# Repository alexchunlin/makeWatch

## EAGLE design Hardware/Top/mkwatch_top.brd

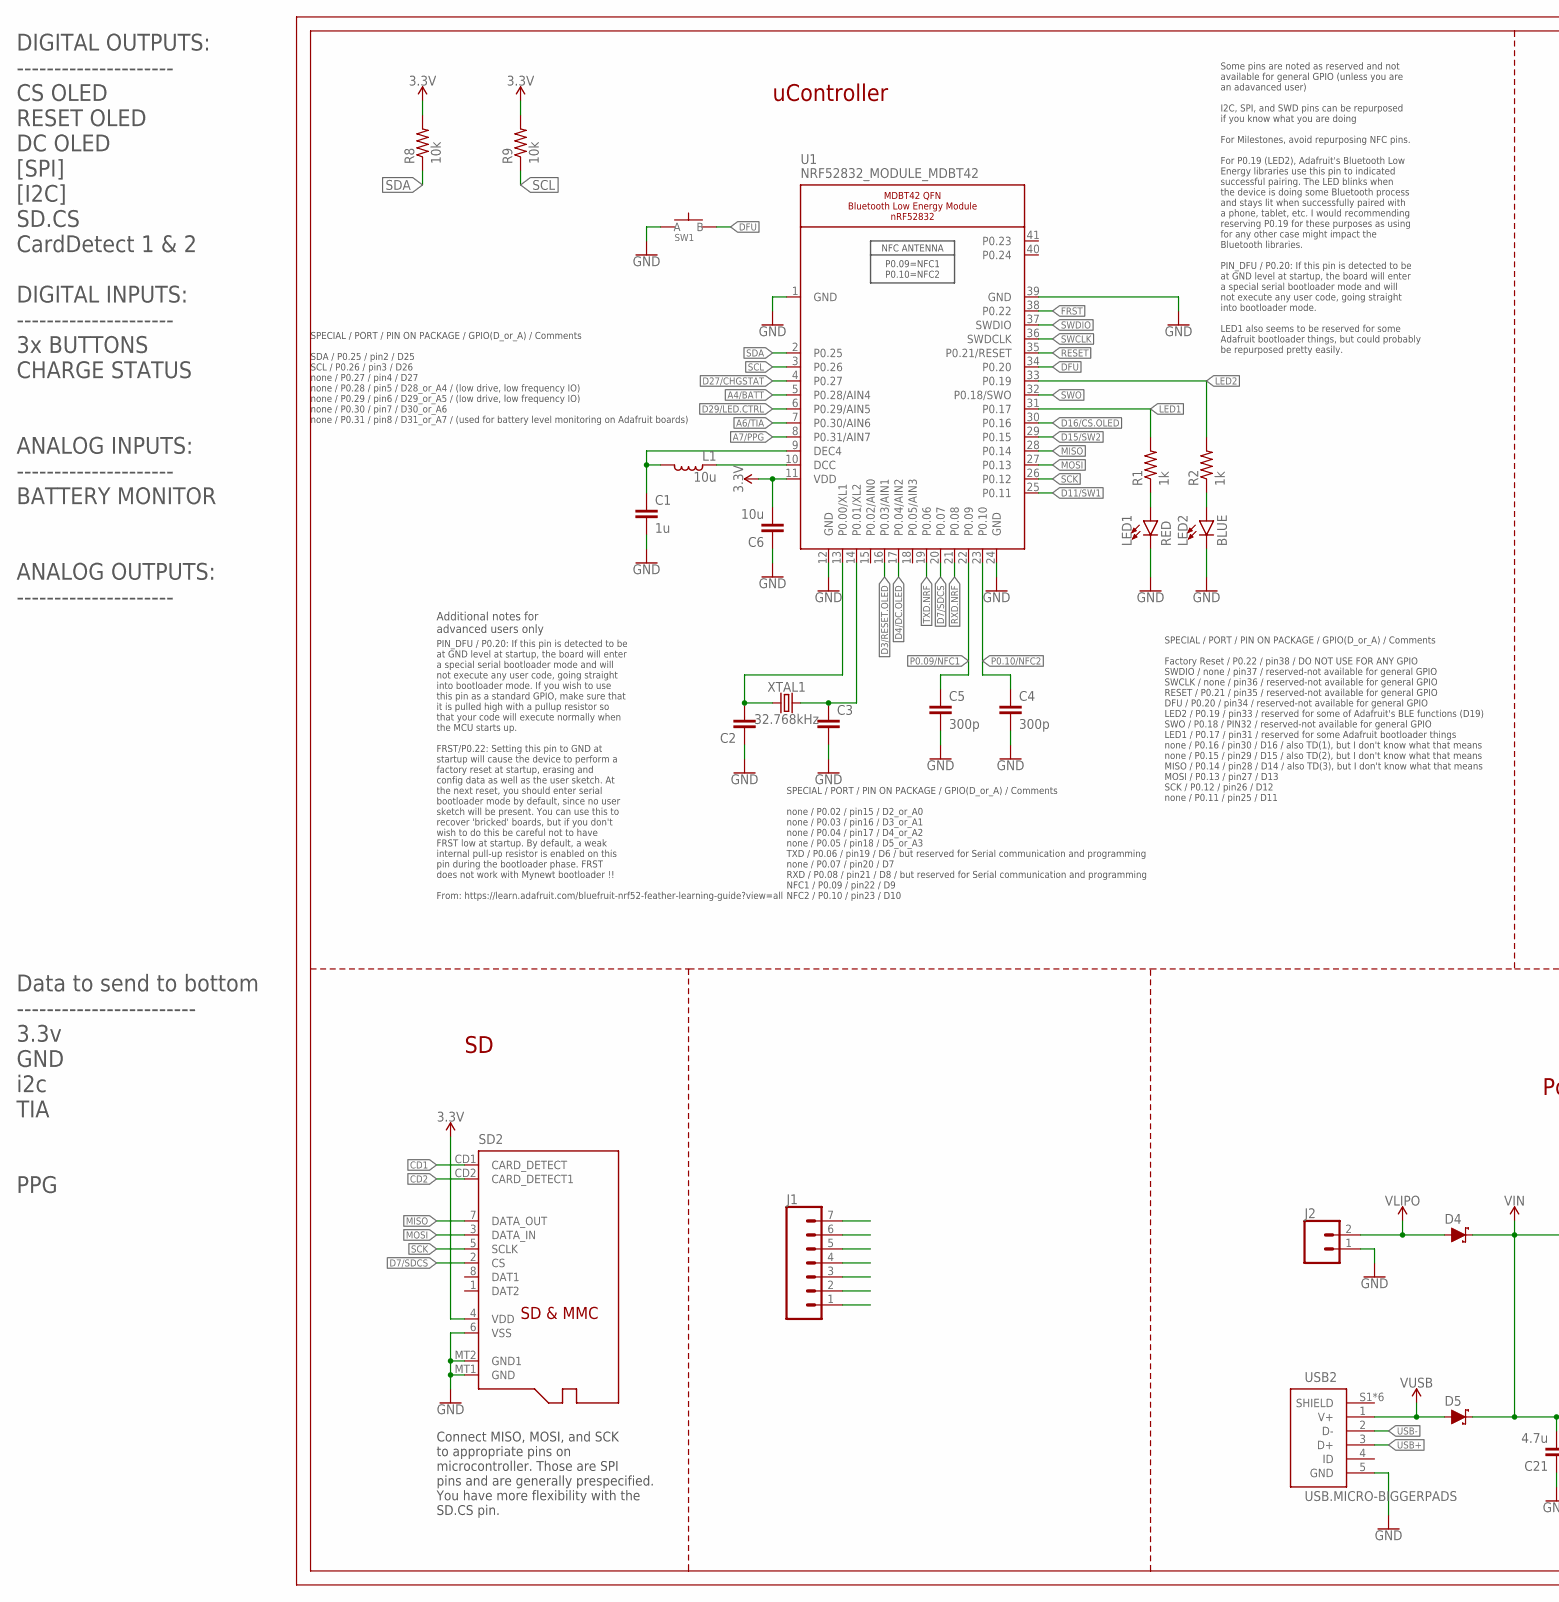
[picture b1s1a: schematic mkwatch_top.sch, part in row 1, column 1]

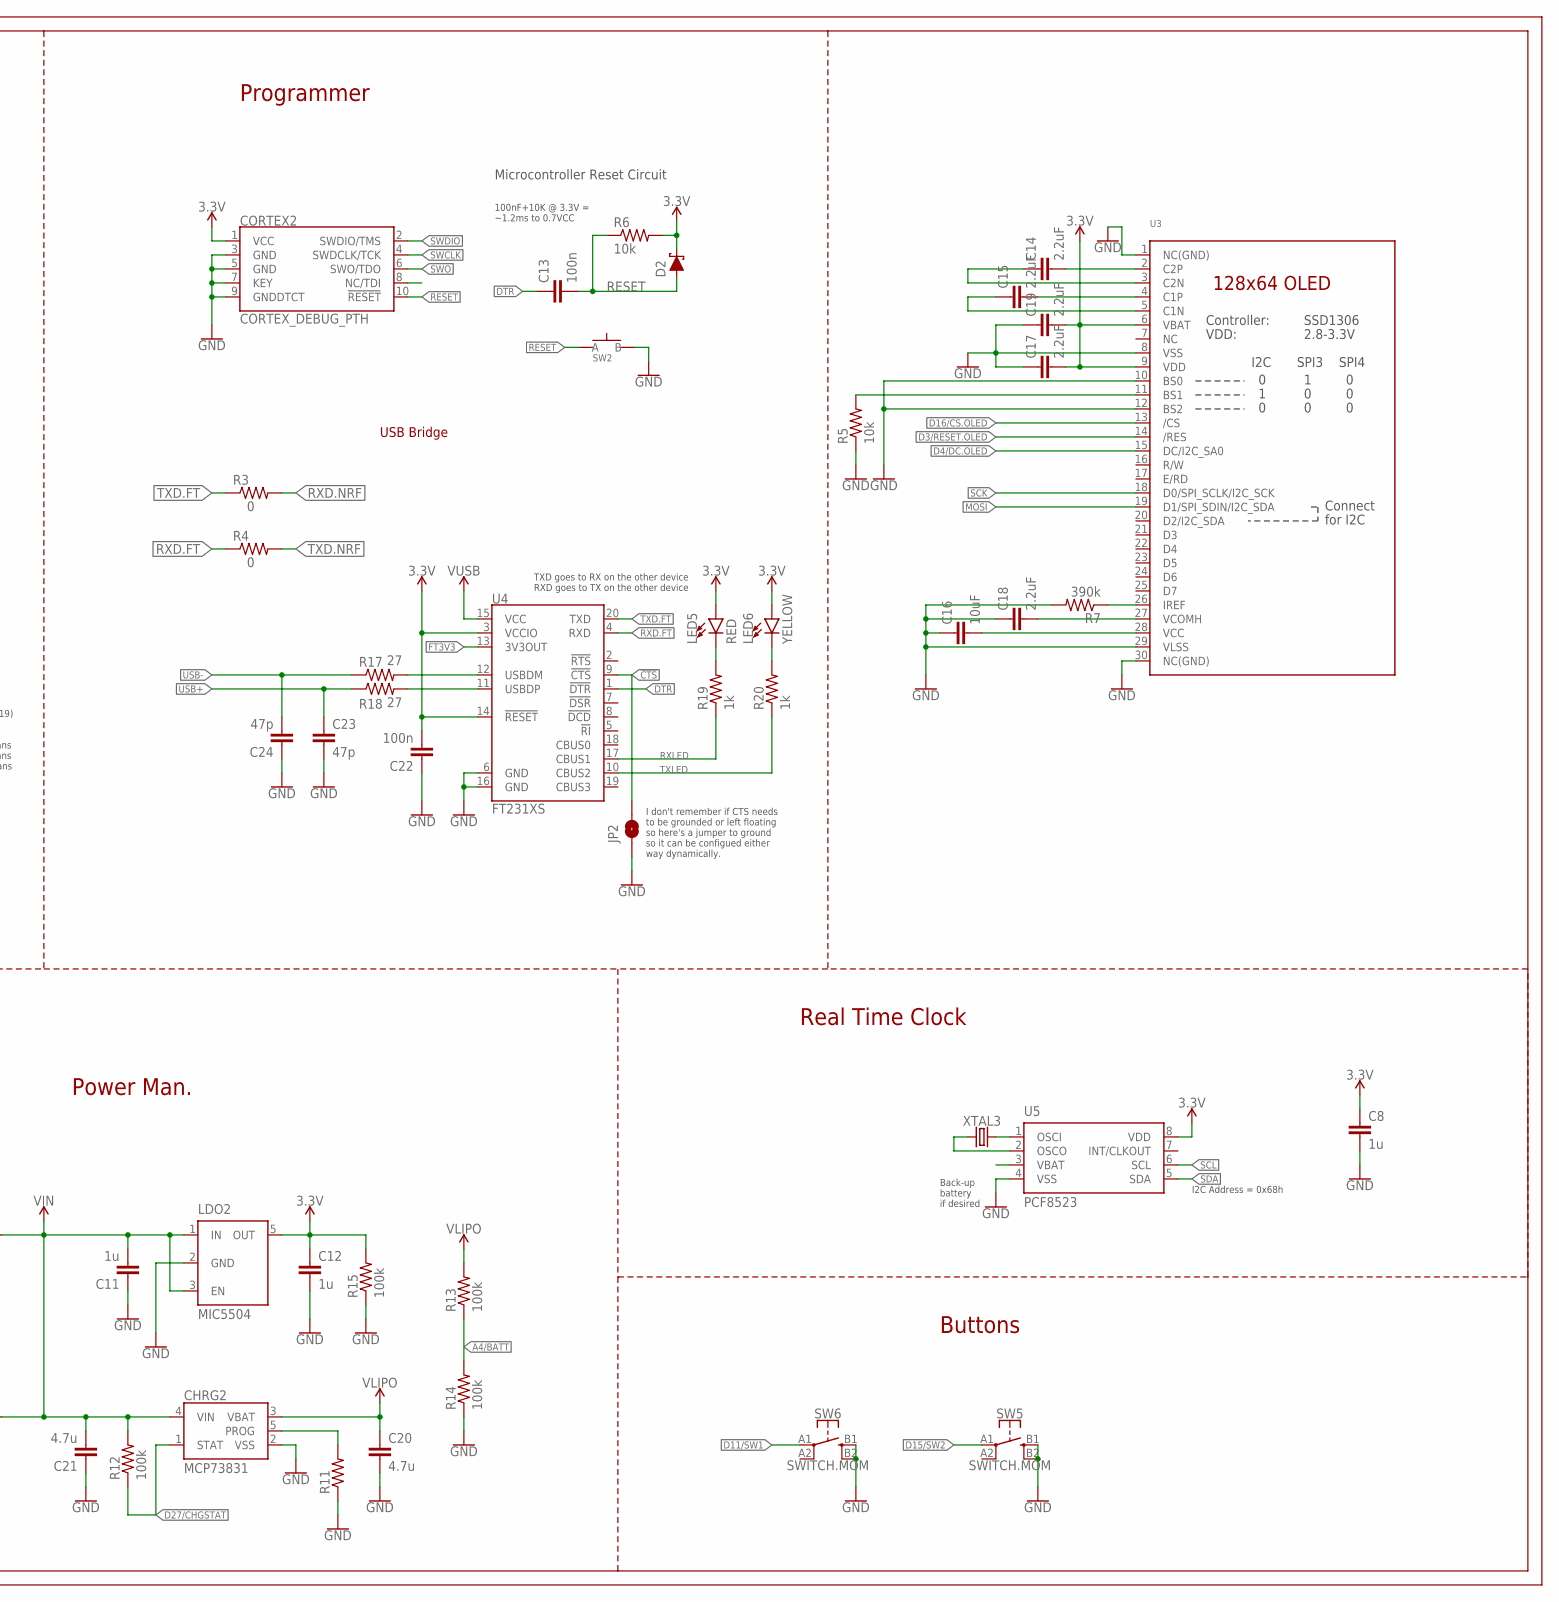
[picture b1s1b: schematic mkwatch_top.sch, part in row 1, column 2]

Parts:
C1, C8, C11, C12: 1u; C0603
C2, C3: CAPACITOR0603; C0603
C4, C5: 300p; C0603
C6: 10u; C0805
C13, C22: 100n; C0603
C14, C15, C17, C18, C19: 2.2uF; C0402
C16: 10uF; C0603
C20, C21: 4.7u; C0603
C23, C24: 47p; C0603
CHRG2: MCP73831; SOT23-5
CORTEX2: CORTEX_DEBUG_PTH; 2X5-PTH-1.27MM
D2, D4, D5: SCHOTTKY-USC; USC
J1: CONN_07-1.27MM; 1X07_1.27MM
J2: CONN_02; 1X02
JP2: JUMPER-SMT_2_NO_SILK; SMT-JUMPER_2_NO_SILK
L1: 10u; L0603
LDO2: MIC5504; SOT23-5
LED1, LED5: RED; LED-0603
LED2: BLUE; LED-0603
LED6: YELLOW; LED-0603
R1, R2, R19, R20: 1k; R0603
R3, R4: 0; R0402
R5, R6: 10k; R0603
R7: 390k; R0603
R8, R9: 10k; R0402
R11: RESISTOR0603; R0603
R12, R13, R14, R15: 100k; R0603
R17, R18: 27; R0603
SD2: MICROSD
SW1, SW2: SPST-PTS830GG140-COPY.1-3; BUTTON-GULLWING
SW5, SW6: SWITCH.MOM; TACTILE_SWITCH_SMD_6.2MM_TALL
U1: NRF52832_MODULE_MDBT42; BLE_MODULE_RAYTAC_MDBT42
U3: DISP_OLED_UG-2864HSWEG01-NO-WRAPAROUND; UG-2864HSWEG01_0.96IN_NO-WRAPAROUND
U4: FT231XS; SSOP20_L
U5: PCF8523; SO8; DIGIKEY 568-5306-1-ND
USB2: USB.MICRO-BIGGERPADS; USB-MICRO-01.BIGGERPADS
XTAL1: 32.768kHz; 2-SMD.NOLEAD.2.0MMTO1.2MM
XTAL3: 32.7680kHz; 2-SMD.NOLEAD.2.0MMTO1.2MM

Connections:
3.3V: C6.2, C8.1, C12.1, C17.2, C19.2, C22.2, CORTEX2.1 (VCC), D2.- (C), LDO2.5 (OUT), LED5.A, LED6.A, R6.2, R8.2, R9.2, R15.2, SD2.4 (VDD), U1.11 (VDD), U3.6 (VBAT), U3.9 (VDD), U4.3 (VCCIO), U4.14 (!RESET), U5.8 (VDD)
!CTS: JP2.2, U4.9 (!CTS)
A4/BATT: R13.1, R14.2, U1.5 (P0.28/AIN4)
A6/TIA: U1.7 (P0.30/AIN6)
A7/PPG: U1.8 (P0.31/AIN7)
CD1: SD2.CD1 (CARD_DETECT)
CD2: SD2.CD2 (CARD_DETECT1)
D3/RESET.OLED: U1.16 (P0.03/AIN1), U3.14 (/RES)
D4/DC.OLED: U1.17 (P0.04/AIN2), U3.15 (DC/I2C_SA0)
D7/SDCS: SD2.2 (CS), U1.20 (P0.07)
D11/SW1: SW6.A1 (1), U1.25 (P0.11)
D15/SW2: SW5.A1 (1), U1.29 (P0.15)
D16/CS.OLED: U1.30 (P0.16), U3.13 (/CS)
D27/CHGSTAT: CHRG2.1 (STAT), R12.1, U1.4 (P0.27)
D29/LED.CTRL: U1.6 (P0.29/AIN5)
DFU: SW1.3 (B), U1.34 (P0.20)
DTR: C13.1, U4.1 (!DTR)
FRST: U1.38 (P0.22)
FT3V3: U4.13 (3V3OUT)
GND: C1.2, C2.1, C3.2, C4.2, C5.2, C6.1, C8.2, C11.1, C12.2, C16.1, C17.1, C18.1, C19.1, C20.2, C21.1, C22.1, C23.2, C24.1, CHRG2.2 (VSS), CORTEX2.3 (GND), CORTEX2.5 (GND), CORTEX2.7 (KEY), CORTEX2.9 (GNDDTCT), J2.1, JP2.1, LDO2.2 (GND), LED1.C, LED2.C, R5.1, R7.2, R11.1, R14.1, R15.1, SD2.6 (VSS), SD2.MT1 (GND), SD2.MT2 (GND1), SW1.1 (A), SW2.3 (B), SW5.B1 (3), SW5.B2 (4), SW6.B1 (3), SW6.B2 (4), U1.1 (GND), U1.12 (GND), U1.24 (GND), U1.39 (GND), U3.1 (NC(GND)), U3.8 (VSS), U3.10 (BS0), U3.12 (BS2), U3.29 (VLSS), U3.30 (NC(GND)), U4.6 (GND), U4.16 (GND), U5.4 (VSS), USB2.5 (GND)
LED1: R1.2, U1.31 (P0.17)
LED2: R2.2, U1.33 (P0.19)
MISO: SD2.7 (DATA_OUT), U1.28 (P0.14)
MOSI: SD2.3 (DATA_IN), U1.27 (P0.13), U3.19 (D1/SPI_SDIN/I2C_SDA)
unnamed: C2.2, U1.13 (P0.00/XL1), XTAL1.P$1 (1)
unnamed: C3.1, U1.14 (P0.01/XL2), XTAL1.P$2 (2)
unnamed: L1.1, U1.10 (DCC)
unnamed: R5.2, U3.11 (BS1)
unnamed: LED1.A, R1.1
unnamed: R7.1, U3.26 (IREF)
unnamed: LED2.A, R2.1
unnamed: C1.1, L1.2, U1.9 (DEC4)
unnamed: C14.2, U3.2 (C2P)
unnamed: C14.1, U3.3 (C2N)
unnamed: C15.2, U3.4 (C1P)
unnamed: C15.1, U3.5 (C1N)
unnamed: C16.2, U3.28 (VCC)
unnamed: C18.2, U3.27 (VCOMH)
unnamed: CHRG2.5 (PROG), R11.2
unnamed: U5.2 (OSCO), XTAL3.P$1 (1)
unnamed: U5.1 (OSCI), XTAL3.P$2 (2)
unnamed: R17.2, U4.12 (USBDM)
unnamed: R18.2, U4.11 (USBDP)
unnamed: LED5.C, R19.2
unnamed: LED6.C, R20.2
P0.09/NFC1: C5.1, U1.22 (P0.09)
P0.10/NFC2: C4.1, U1.23 (P0.10)
RESET: C13.2, CORTEX2.10 (!RESET), D2.+ (A), R6.1, SW2.1 (A), U1.35 (P0.21/RESET)
RXD.FT: R4.1, U4.4 (RXD)
RXD.NRF: R3.2, U1.21 (P0.08)
RXLED: R19.1, U4.17 (CBUS1)
SCK: SD2.5 (SCLK), U1.26 (P0.12), U3.18 (D0/SPI_SCLK/I2C_SCK)
SCL: R9.1, U1.3 (P0.26), U5.6 (SCL)
SDA: R8.1, U1.2 (P0.25), U5.5 (SDA)
SWCLK: CORTEX2.4 (SWDCLK/TCK), U1.36 (SWDCLK)
SWDIO: CORTEX2.2 (SWDIO/TMS), U1.37 (SWDIO)
SWO: CORTEX2.6 (SWO/TDO), U1.32 (P0.18/SWO)
TXD.FT: R3.1, U4.20 (TXD)
TXD.NRF: R4.2, U1.19 (P0.06)
TXLED: R20.1, U4.10 (CBUS2)
USB+: C23.1, R18.1, USB2.3 (D+)
USB-: C24.2, R17.1, USB2.2 (D-)
VBATT: U5.3 (VBAT)
VIN: C11.2, C21.2, CHRG2.4 (VIN), D4.- (C), D5.- (C), LDO2.1 (IN), LDO2.3 (EN), R12.2
VLIPO: C20.1, CHRG2.3 (VBAT), D4.+ (A), J2.2, R13.2
V_USB: D5.+ (A), U4.15 (VCC), USB2.1 (V+)

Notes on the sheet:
uController
Programmer
Power Man.
Buttons
I2C Address = 0x68h
Back-up battery if desired
Real Time Clock
DIGITAL OUTPUTS: --------------------- CS OLED RESET OLED DC OLED [SPI] [I2C] SD.CS CardDetect 1 & 2 DIGITAL INPUTS: --------------------- 3x BUTTONS CHARGE STATUS ANALOG INPUTS: --------------------- BATTERY MONITOR ANALOG OUTPUTS: ---------------------
Data to send to bottom ------------------------ 3.3v GND i2c TIA PPG
Microcontroller Reset Circuit
100nF+10K @ 3.3V = ~1.2ms to 0.7VCC
SPECIAL / PORT / PIN ON PACKAGE / GPIO(D_or_A) / Comments SDA / P0.25 / pin2 / D25 SCL / P0.26 / pin3 / D26 none / P0.27 / pin4 / D27 none / P0.28 / pin5 / D28_or_A4 / (low drive, low frequency IO) none / P0.29 / pin6 / D29_or_A5 / (low drive, low frequency IO) none / P0.30 / pin7 / D30_or_A6 none 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
SPECIAL / PORT / PIN ON PACKAGE / GPIO(D_or_A) / Comments none / P0.02 / pin15 / D2_or_A0 none / P0.03 / pin16 / D3_or_A1 none / P0.04 / pin17 / D4_or_A2 none / P0.05 / pin18 / D5_or_A3 TXD / P0.06 / pin19 / D6 / but reserved for Serial communication and programming none / P0.07 / pin20 / D7 RXD / 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
SPECIAL / PORT / PIN ON PACKAGE / GPIO(D_or_A) / Comments Factory Reset / P0.22 / pin38 / DO NOT USE FOR ANY GPIO SWDIO / none / pin37 / reserved-not available for general GPIO SWCLK / none / pin36 / reserved-not available for general GPIO RESET / P0.21 / pin35 / reserved-not available for general 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
Some pins are noted as reserved and not available for general GPIO (unless you are an adavanced user) I2C, SPI, and SWD pins can be repurposed if you know what you are doing For Milestones, avoid repurposing NFC pins. For P0.19 (LED2), Adafruit's Bluetooth Low Energy libraries use this pin to indic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
PIN_DFU / P0.20: If this pin is detected to be at GND level at startup, the board will enter a special serial bootloader mode and will not execute any user code, going straight into bootloader mode. If you wish to use this pin as a standard GPIO, make sure that it is pulled high with a pullup resis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
Additional notes for advanced users only
Connect MISO, MOSI, and SCK to appropriate pins on microcontroller. Those are SPI pins and are generally prespecified. You have more flexibility with the SD.CS pin.
TXD goes to RX on the other device RXD goes to TX on the other device
I don't remember if CTS needs to be grounded or left floating so here's a jumper to ground so it can be configued either way dynamically.
USB Bridge

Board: 2 copper layers, 65 parts (2 on the bottom side), 58 nets, no tracks yet.

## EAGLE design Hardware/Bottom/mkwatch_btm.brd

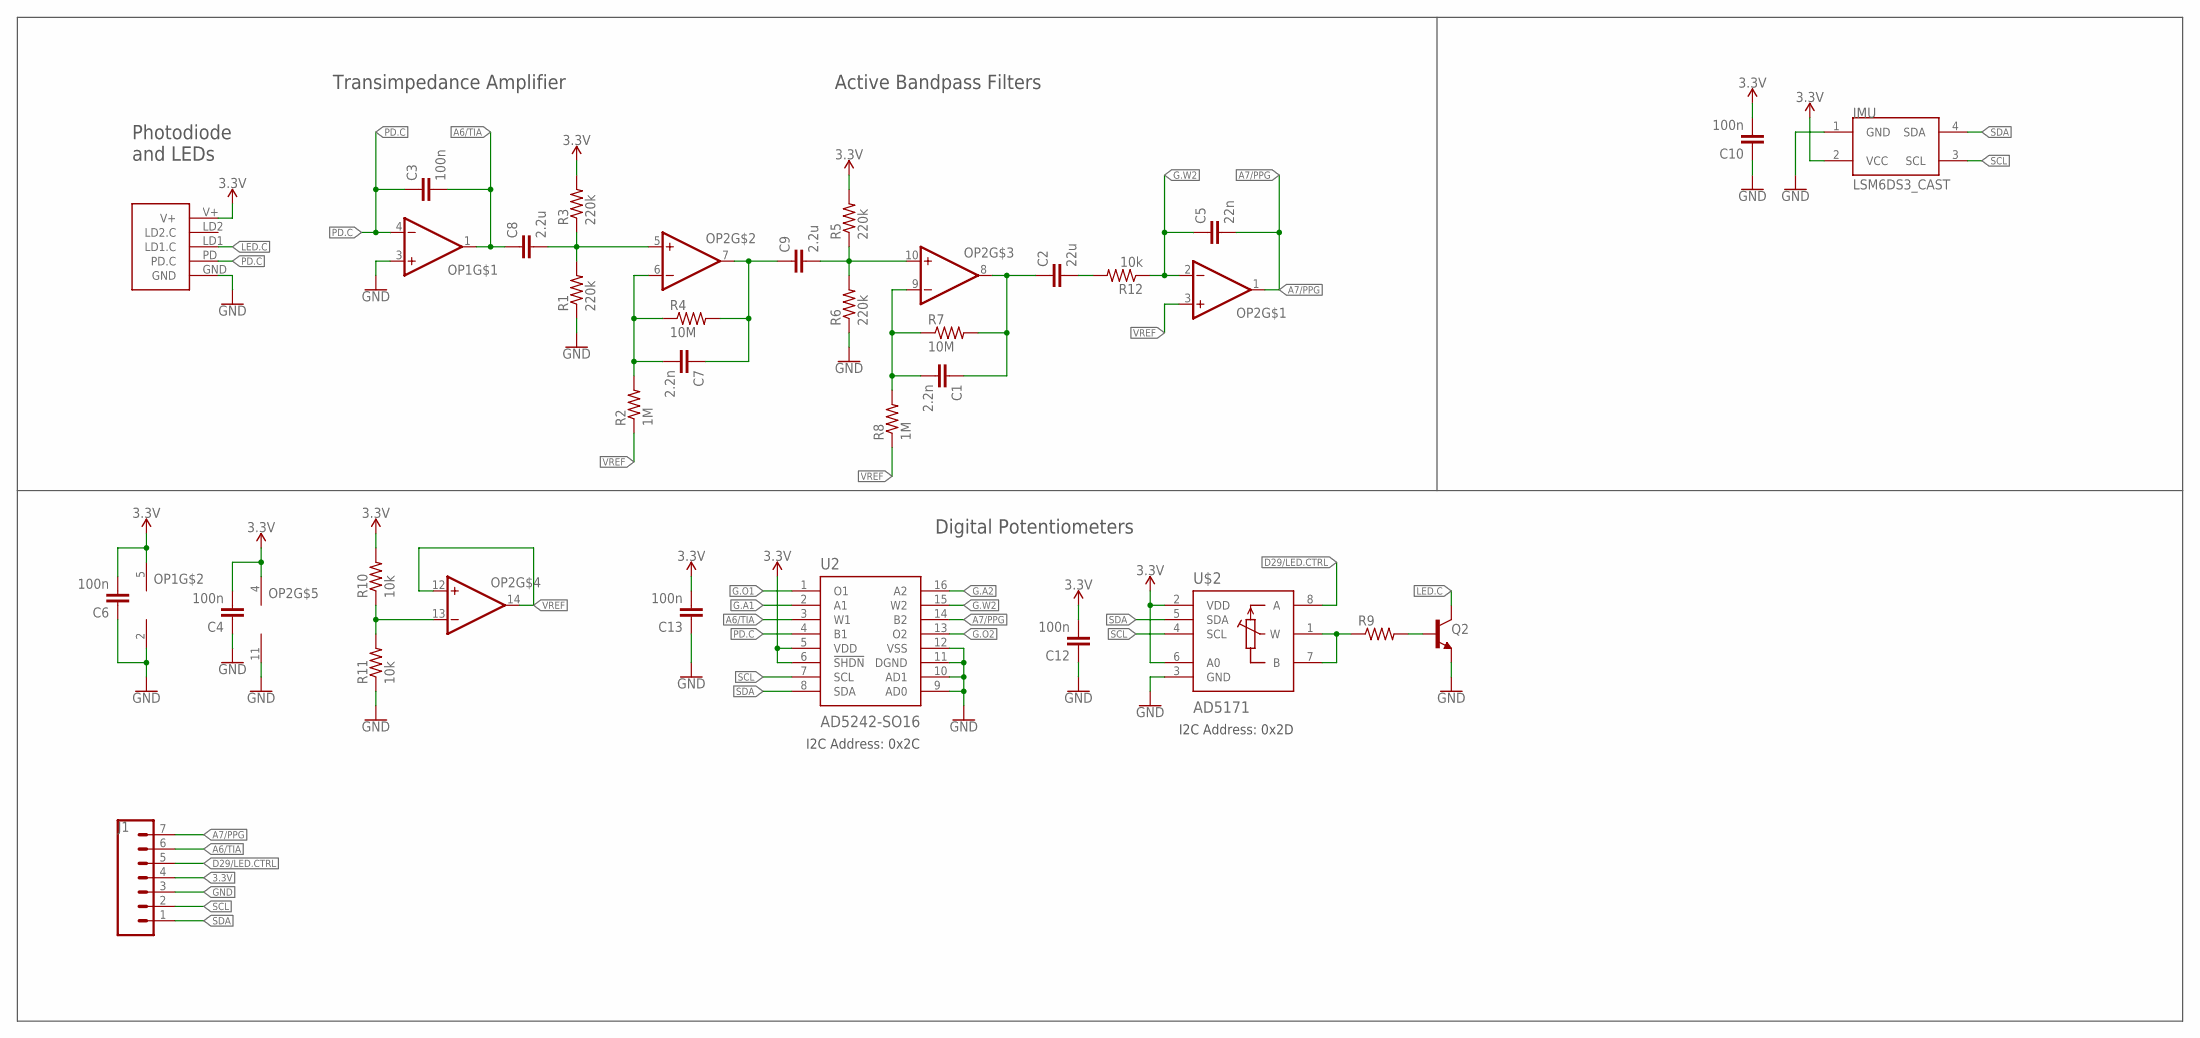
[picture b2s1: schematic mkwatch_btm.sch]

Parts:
C1, C7: 2.2n; C0603
C2: 22u; C0603
C3, C4, C6, C10, C12, C13: 100n; C0603
C5: 22n; C0603
C8, C9: 2.2u; C0603
IMU: LSM6DS3_CAST
J1: CONN_07-1.27MM; 1X07_1.27MM
OP1: OP-SINGLEOT; SOT23-5
OP2: OP-QUAD-SO14; SO14
Q2: NPN-GENERIC; SOT23-3
R1, R3, R5, R6: 220k; R0603
R2, R8: 1M; R0603
R4, R7: 10M; R0603
R9: RESISTOR0603; R0603
R10, R11: 10k; R0402
R12: 10k; R0603
U2: AD5242-SO16; SO16
U$1: PPG.MODULE.2
U$2: AD5171; SOT-23-8

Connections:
3.3V: C4.2, C6.2, C10.2, C12.2, C13.2, IMU.2 (VCC), J1.4, OP1.5 (V+), OP2.4 (V+), R3.2, R5.2, R10.2, U2.5 (VDD), U2.6 (!SHDN), U$1.V+, U$2.2 (VDD), U$2.6 (A0)
A6/TIA: C3.2, C8.1, J1.6, OP1.1 (OUT), U2.3 (W1)
A7/PPG: C5.2, J1.7, OP2.1 (OUT), U2.14 (B2)
D29/LED.CTRL: J1.5, U$2.8 (A)
G.A1: U2.2 (A1)
G.A2: U2.16 (A2)
G.O1: U2.1 (O1)
G.O2: U2.13 (O2)
G.W2: C5.1, OP2.2 (-IN), R12.1, U2.15 (W2)
GND: C4.1, C6.1, C10.1, C12.1, C13.1, IMU.1 (GND), J1.3, OP1.2 (V-), OP1.3 (+IN), OP2.11 (V-), Q2.2 (E), R1.1, R6.1, R11.1, U2.9 (AD0), U2.10 (AD1), U2.11 (DGND), U2.12 (VSS), U$1.GND, U$2.3 (GND)
LED.C: Q2.3 (C), U$1.LD1 (LD1.C)
unnamed: C8.2, OP2.5 (+IN), R1.2, R3.1
unnamed: C9.2, OP2.10 (+IN), R5.1, R6.2
unnamed: C7.2, OP2.6 (-IN), R2.2, R4.1
unnamed: C7.1, C9.1, OP2.7 (OUT), R4.2
unnamed: C1.2, OP2.9 (-IN), R7.1, R8.2
unnamed: C1.1, C2.1, OP2.8 (OUT), R7.2
unnamed: C2.2, R12.2
unnamed: Q2.1 (B), R9.2
unnamed: R9.1, U$2.1 (W), U$2.7 (B)
unnamed: OP2.13 (-IN), R10.1, R11.2
PD.C: C3.1, OP1.4 (-IN), U2.4 (B1), U$1.PD (PD.C)
SCL: IMU.3 (SCL), J1.2, U2.7 (SCL), U$2.4 (SCL)
SDA: IMU.4 (SDA), J1.1, U2.8 (SDA), U$2.5 (SDA)
VREF: OP2.3 (+IN), OP2.12 (+IN), OP2.14 (OUT), R2.1, R8.1

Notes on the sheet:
Photodiode and LEDs
Active Bandpass Filters
Digital Potentiometers
Transimpedance Amplifier
I2C Address: 0x2C
I2C Address: 0x2D

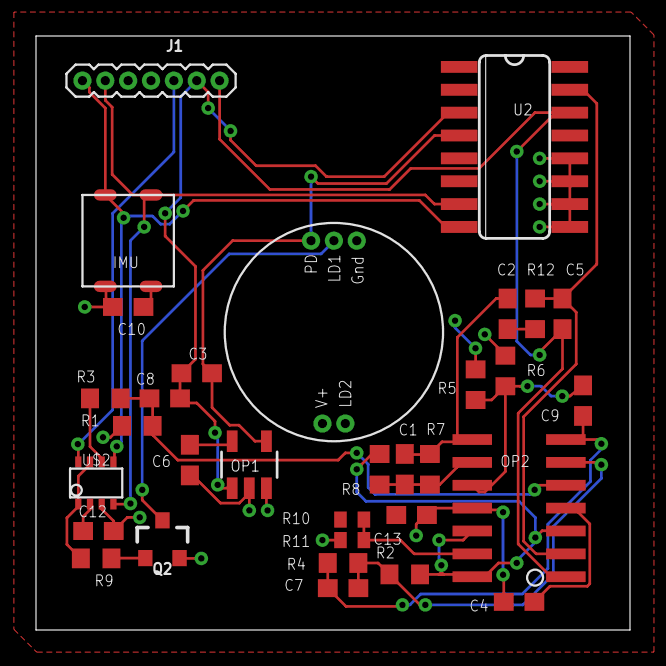
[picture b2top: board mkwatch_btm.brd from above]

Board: 2 copper layers, 33.0 x 33.0 mm, 32 parts (0 on the bottom side), 21 nets.

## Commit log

2020-05-29 Create makeWatch.txt
    Features list
2020-06-04 added files for Microcontroller
2020-06-29 Completed Bottom board routing. Added bottom board schematic. Added top board schematic.
2020-06-29 added 7pin connector to schematic and board for comm between top and bottom board
2020-07-02 WIP - positioned main components on top and bottom, starting to re arrange passives before routing begins
